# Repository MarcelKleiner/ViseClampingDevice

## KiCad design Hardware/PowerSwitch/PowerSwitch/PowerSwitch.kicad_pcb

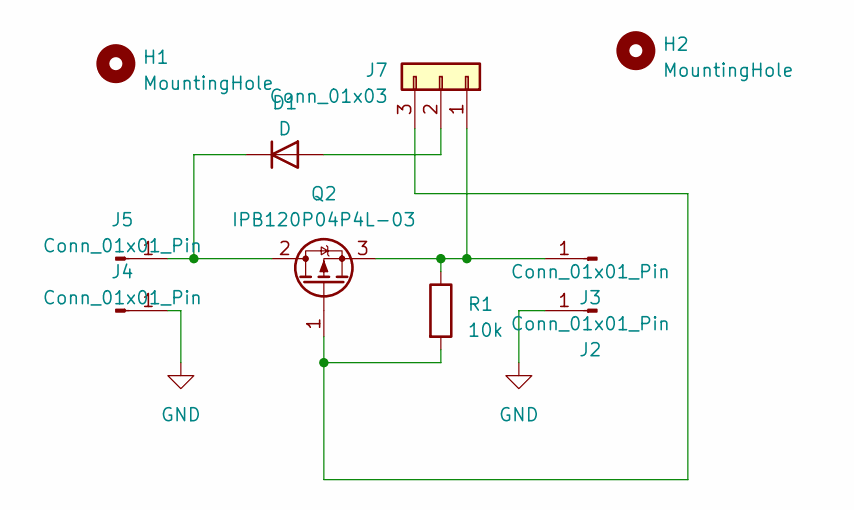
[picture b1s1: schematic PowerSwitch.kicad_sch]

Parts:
D1: D; D_1206_3216Metric
H1, H2: MountingHole; MountingHole_3.2mm_M3
J2, J3, J4, J5: Conn_01x01_Pin; MountingHole_3.2mm_M3_Pad_Via
J7: Conn_01x03; TerminalBlock_Phoenix_MPT-0,5-3-2.54_1x03_P2.54mm_Horizontal
Q2: IPB120P04P4L-03; TO-220-3_Vertical
R1: 10k; R_1206_3216Metric

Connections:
GND: J2.1, J4.1
unnamed: D1.2 (A), J7.2
unnamed: D1.1 (K), J5.1, Q2.2 (D)
unnamed: J3.1, J7.1, Q2.3 (S), R1.1
unnamed: J7.3, Q2.1 (G), R1.2

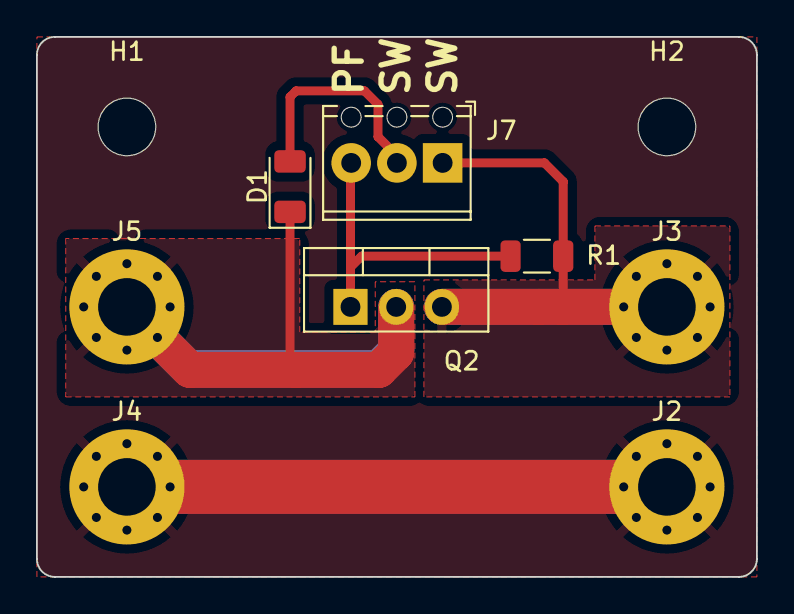
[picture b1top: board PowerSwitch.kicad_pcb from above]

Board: 2 copper layers, 40.0 x 30.0 mm, 10 parts (0 on the bottom side), 5 nets.

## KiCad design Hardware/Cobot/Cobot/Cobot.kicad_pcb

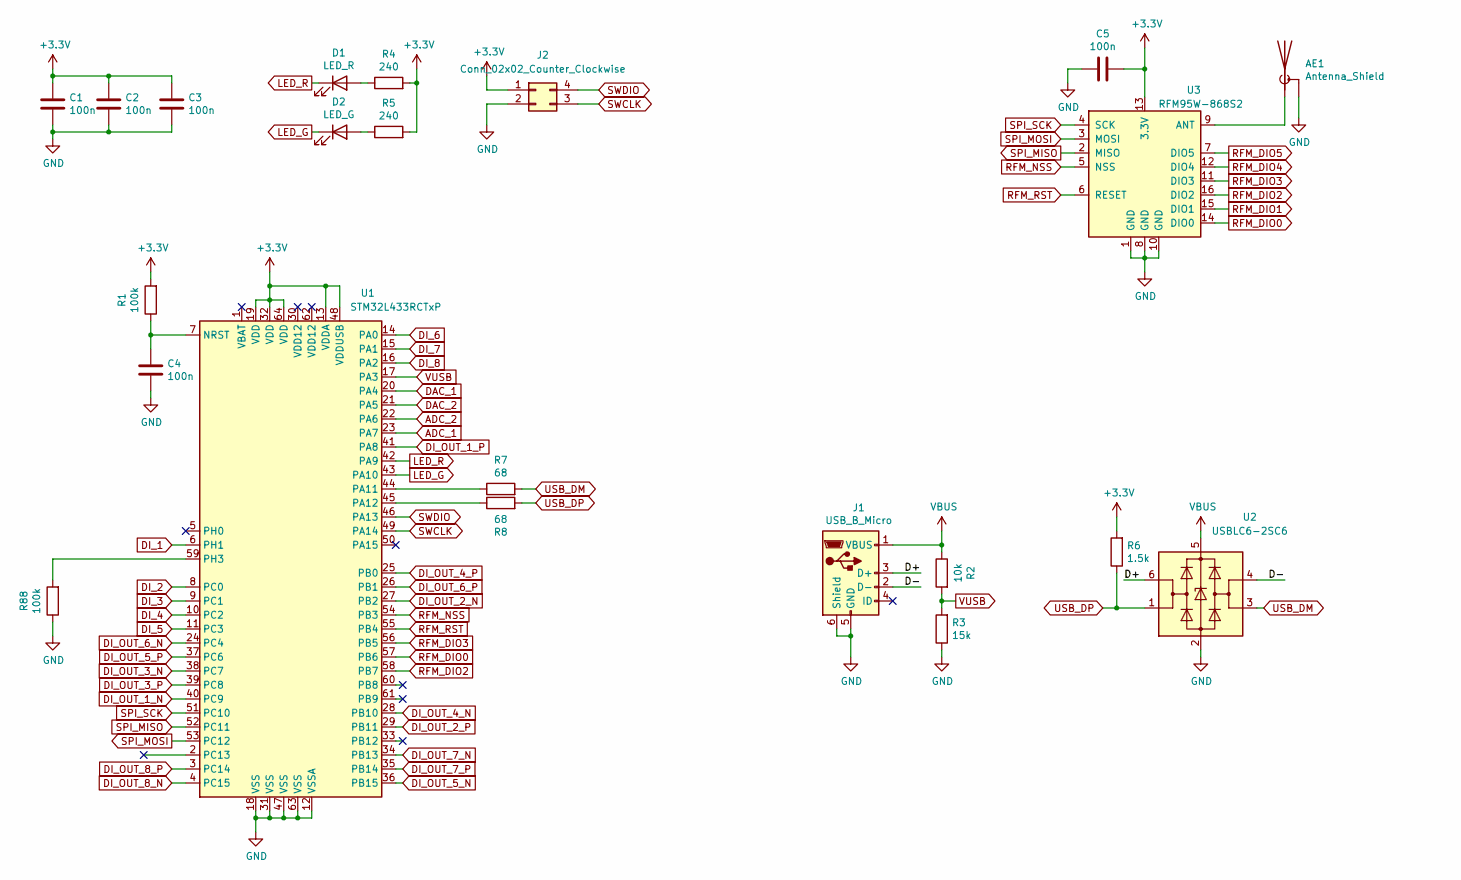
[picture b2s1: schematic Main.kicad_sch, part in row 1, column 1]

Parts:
AE1: Antenna_Shield; U.FL_Hirose_U.FL-R-SMT-1_Vertical; Mouser Nr. 712-CONUFL001-SMD-T
C1, C2, C3, C4, C5: 100n; C_0603_1608Metric; Mouser Nr. 187-CL10B104KB8NNWC
D1: LED_R; LED_0603_1608Metric; Mouser Nr. 696-SMLLXFP0603SICTR
D2: LED_G; LED_0603_1608Metric; Mouser Nr. 696-SMLLXFP0603SUGCT
J1: USB_B_Micro; USB_Micro-B_Wuerth_614105150721_Vertical; Mouser Nr. 710-614105150721
J2: Conn_02x02_Counter_Clockwise; PinHeader_2x02_P2.54mm_Vertical
R1, R88: 100k; R_0603_1608Metric; Mouser Nr. 71-CRCW0603100KFKEAC
R2: 10k; R_0603_1608Metric; Mouser Nr. 603-RT0603FRE0710KL
R3: 15k; R_0603_1608Metric; Mouser Nr. 667-ERJ-3EKF1502V
R4, R5: 240; R_0603_1608Metric; Mouser Nr. 603-RC0603FR-13240RL
R6: 1.5k; R_0603_1608Metric; Mouser Nr. 603-RT0603FRE101K5L
R7, R8: 68; R_0603_1608Metric; Mouser Nr. 603-RC0603JR-0768RL
U1: STM32L433RCTxP; LQFP-64_10x10mm_P0.5mm; Mouser Nr. 511-STM32L433RCT6P
U2: USBLC6-2SC6; SOT-23-6; Mouser Nr. 511-USBLC6-2SC6
U3: RFM95W-868S2; HOPERF_RFM9XW_SMD; Mouser Nr. 223-RFM95W-868S2

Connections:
+3.3V: C1.1, C2.1, C3.1, C5.2, J2.1, R1.2, R4.2, R5.2, R6.2, U1.13 (VDDA), U1.19 (VDD), U1.32 (VDD), U1.48 (VDDUSB), U1.64 (VDD), U3.13 (3.3V); also elsewhere on the board
/Main/D+: J1.3 (D+), U2.6 (I/O1)
/Main/D-: J1.2 (D-), U2.4 (I/O2)
ADC_1: U1.23 (PA7); also elsewhere on the board
ADC_2: U1.22 (PA6); also elsewhere on the board
DAC_1: U1.20 (PA4); also elsewhere on the board
DAC_2: U1.21 (PA5); also elsewhere on the board
DI_1: U1.6 (PH1); also elsewhere on the board
DI_2: U1.8 (PC0); also elsewhere on the board
DI_3: U1.9 (PC1); also elsewhere on the board
DI_4: U1.10 (PC2); also elsewhere on the board
DI_5: U1.11 (PC3); also elsewhere on the board
DI_6: U1.14 (PA0); also elsewhere on the board
DI_7: U1.15 (PA1); also elsewhere on the board
DI_8: U1.16 (PA2); also elsewhere on the board
DI_OUT_1_N: U1.40 (PC9); also elsewhere on the board
DI_OUT_1_P: U1.41 (PA8); also elsewhere on the board
DI_OUT_2_N: U1.27 (PB2); also elsewhere on the board
DI_OUT_2_P: U1.29 (PB11); also elsewhere on the board
DI_OUT_3_N: U1.38 (PC7); also elsewhere on the board
DI_OUT_3_P: U1.39 (PC8); also elsewhere on the board
DI_OUT_4_N: U1.28 (PB10); also elsewhere on the board
DI_OUT_4_P: U1.25 (PB0); also elsewhere on the board
DI_OUT_5_N: U1.36 (PB15); also elsewhere on the board
DI_OUT_5_P: U1.37 (PC6); also elsewhere on the board
DI_OUT_6_N: U1.24 (PC4); also elsewhere on the board
DI_OUT_6_P: U1.26 (PB1); also elsewhere on the board
DI_OUT_7_N: U1.34 (PB13); also elsewhere on the board
DI_OUT_7_P: U1.35 (PB14); also elsewhere on the board
DI_OUT_8_N: U1.4 (PC15); also elsewhere on the board
DI_OUT_8_P: U1.3 (PC14); also elsewhere on the board
LED_G: D2.1 (K), U1.43 (PA10)
LED_R: D1.1 (K), U1.42 (PA9)
unnamed: AE1.1 (A), U3.9 (ANT)
unnamed: D1.2 (A), R4.1
unnamed: D2.2 (A), R5.1
unnamed: C4.1, R1.1, U1.7 (NRST)
unnamed: R7.1, U1.44 (PA11)
unnamed: R8.1, U1.45 (PA12)
unnamed: R88.2, U1.59 (PH3)
RFM_DIO0: U1.57 (PB6), U3.14 (DIO0)
RFM_DIO1: U3.15 (DIO1)
RFM_DIO2: U1.58 (PB7), U3.16 (DIO2)
RFM_DIO3: U1.56 (PB5), U3.11 (DIO3)
RFM_DIO4: U3.12 (DIO4)
RFM_DIO5: U3.7 (DIO5)
RFM_NSS: U1.54 (PB3), U3.5 (NSS)
RFM_RST: U1.55 (PB4), U3.6 (RESET)
SPI_MISO: U1.52 (PC11), U3.2 (MISO)
SPI_MOSI: U1.53 (PC12), U3.3 (MOSI)
SPI_SCK: U1.51 (PC10), U3.4 (SCK)
SWCLK: J2.3, U1.49 (PA14)
SWDIO: J2.4, U1.46 (PA13)
USB_DM: R7.2, U2.3 (I/O2)
USB_DP: R6.1, R8.2, U2.1 (I/O1)
VBUS: J1.1 (VBUS), R2.1, U2.5 (VBUS); also elsewhere on the board
VUSB: R2.2, R3.2, U1.17 (PA3)

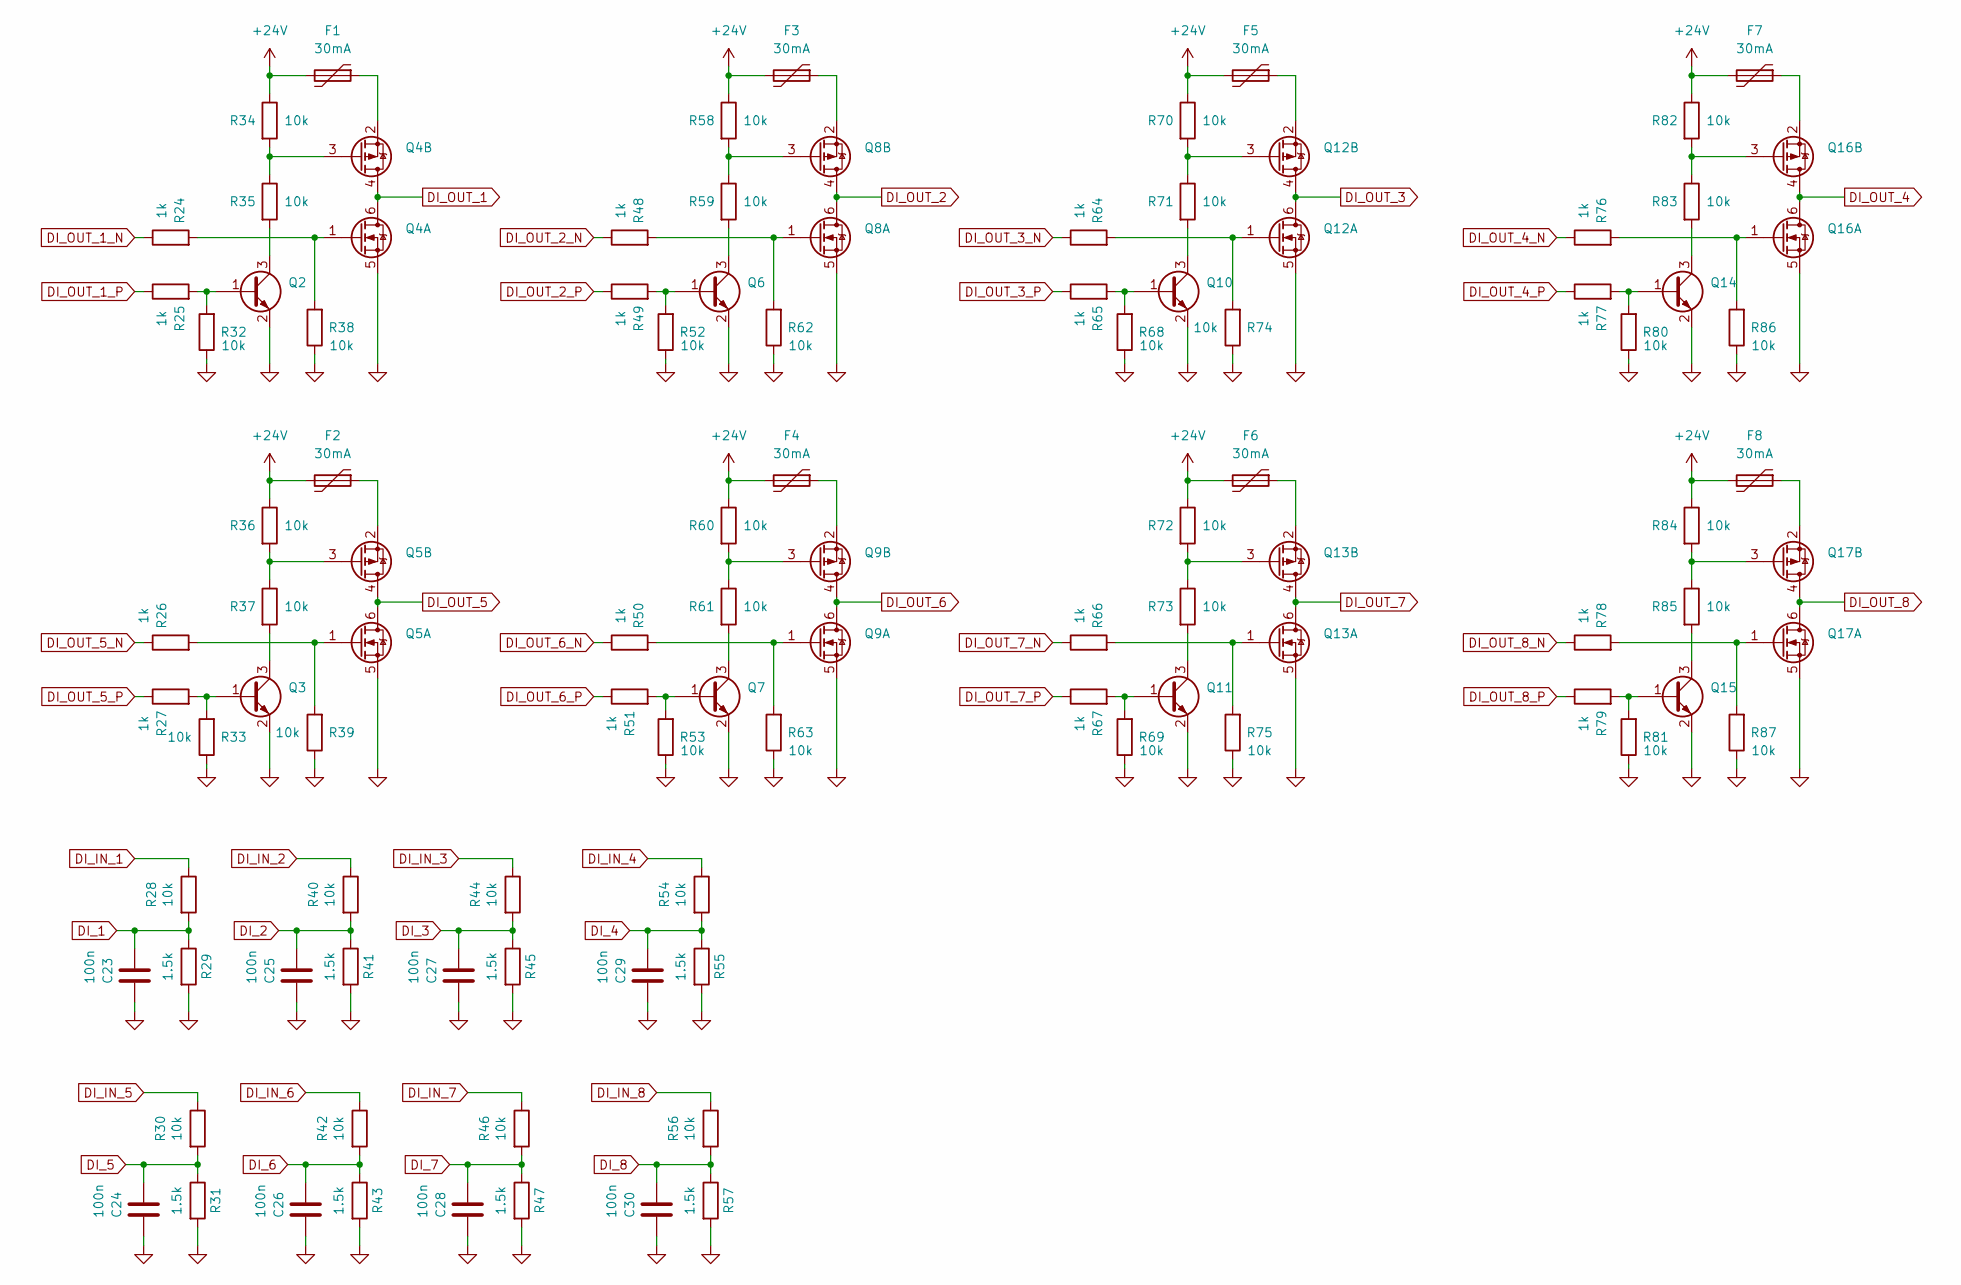
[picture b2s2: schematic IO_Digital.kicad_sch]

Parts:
C23, C24, C25, C26, C27, C28, C29, C30: 100n; C_0603_1608Metric; Mouser Nr. 187-CL10B104KB8NNWC
F1, F2, F3, F4, F5, F6, F7, F8: 30mA; Fuse_0603_1608Metric; Mouser Nr. 530-0ZCM0003FF2G
Q2, Q3, Q6, Q7, Q10, Q11, Q14, Q15: SOT-23; Mouser Nr. 771-BC846A235
Q4, Q5, Q8, Q9, Q12, Q13, Q16, Q17: SOT-23-6; Mouser Nr. 621-DMC2700UDM-7
R24, R25, R26, R27, R48, R49, R50, R51, R64, R65, R66, R67, R76, R77, R78, R79: 1k; R_0603_1608Metric; Mouser Nr. 603-RT0603FRE071KL
R28, R30, R32, R33, R34, R35, R36, R37, R38, R39, R40, R42, R44, R46, R52, R53, R54, R56, R58, R59, R60, R61, R62, R63, R68, R69, R70, R71, R72, R73, R74, R75, R80, R81, R82, R83, R84, R85, R86, R87: 10k; R_0603_1608Metric; Mouser Nr. 603-RT0603FRE0710KL
R29, R31, R41, R43, R45, R47, R55, R57: 1.5k; R_0603_1608Metric; Mouser Nr. 603-RT0603FRE101K5L

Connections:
+24V: F1.2, F2.2, F3.2, F4.2, F5.2, F6.2, F7.2, F8.2, R34.1, R36.1, R58.1, R60.1, R70.1, R72.1, R82.1, R84.1; also elsewhere on the board
DI_1: C23.1, R28.2, R29.1; also elsewhere on the board
DI_2: C25.1, R40.2, R41.1; also elsewhere on the board
DI_3: C27.1, R44.2, R45.1; also elsewhere on the board
DI_4: C29.1, R54.2, R55.1; also elsewhere on the board
DI_5: C24.1, R30.2, R31.1; also elsewhere on the board
DI_6: C26.1, R42.2, R43.1; also elsewhere on the board
DI_7: C28.1, R46.2, R47.1; also elsewhere on the board
DI_8: C30.1, R56.2, R57.1; also elsewhere on the board
DI_IN_1: R28.1; also elsewhere on the board
DI_IN_2: R40.1; also elsewhere on the board
DI_IN_3: R44.1; also elsewhere on the board
DI_IN_4: R54.1; also elsewhere on the board
DI_IN_5: R30.1; also elsewhere on the board
DI_IN_6: R42.1; also elsewhere on the board
DI_IN_7: R46.1; also elsewhere on the board
DI_IN_8: R56.1; also elsewhere on the board
DI_OUT_1: Q4.4 (D), Q4.6 (D); also elsewhere on the board
DI_OUT_1_N: R24.1; also elsewhere on the board
DI_OUT_1_P: R25.1; also elsewhere on the board
DI_OUT_2: Q8.4 (D), Q8.6 (D); also elsewhere on the board
DI_OUT_2_N: R48.1; also elsewhere on the board
DI_OUT_2_P: R49.1; also elsewhere on the board
DI_OUT_3: Q12.4 (D), Q12.6 (D); also elsewhere on the board
DI_OUT_3_N: R64.1; also elsewhere on the board
DI_OUT_3_P: R65.1; also elsewhere on the board
DI_OUT_4: Q16.4 (D), Q16.6 (D); also elsewhere on the board
DI_OUT_4_N: R76.1; also elsewhere on the board
DI_OUT_4_P: R77.1; also elsewhere on the board
DI_OUT_5: Q5.4 (D), Q5.6 (D); also elsewhere on the board
DI_OUT_5_N: R26.1; also elsewhere on the board
DI_OUT_5_P: R27.1; also elsewhere on the board
DI_OUT_6: Q9.4 (D), Q9.6 (D); also elsewhere on the board
DI_OUT_6_N: R50.1; also elsewhere on the board
DI_OUT_6_P: R51.1; also elsewhere on the board
DI_OUT_7: Q13.4 (D), Q13.6 (D); also elsewhere on the board
DI_OUT_7_N: R66.1; also elsewhere on the board
DI_OUT_7_P: R67.1; also elsewhere on the board
DI_OUT_8: Q17.4 (D), Q17.6 (D); also elsewhere on the board
DI_OUT_8_N: R78.1; also elsewhere on the board
DI_OUT_8_P: R79.1; also elsewhere on the board
unnamed: Q2.1 (B), R25.2, R32.2
unnamed: Q2.3 (C), R35.2
unnamed: Q3.1 (B), R27.2, R33.2
unnamed: Q3.3 (C), R37.2
unnamed: Q4.1 (G), R24.2, R38.2
unnamed: Q4.3 (G), R34.2, R35.1
unnamed: F1.1, Q4.2 (S)
unnamed: Q5.1 (G), R26.2, R39.2
unnamed: Q5.3 (G), R36.2, R37.1
unnamed: F2.1, Q5.2 (S)
unnamed: Q6.1 (B), R49.2, R52.2
unnamed: Q6.3 (C), R59.2
unnamed: Q7.1 (B), R51.2, R53.2
unnamed: Q7.3 (C), R61.2
unnamed: Q8.1 (G), R48.2, R62.2
unnamed: Q8.3 (G), R58.2, R59.1
unnamed: F3.1, Q8.2 (S)
unnamed: Q9.1 (G), R50.2, R63.2
unnamed: Q9.3 (G), R60.2, R61.1
unnamed: F4.1, Q9.2 (S)
unnamed: Q10.1 (B), R65.2, R68.2
unnamed: Q10.3 (C), R71.2
unnamed: Q11.1 (B), R67.2, R69.2
unnamed: Q11.3 (C), R73.2
unnamed: Q12.1 (G), R64.2, R74.2
unnamed: Q12.3 (G), R70.2, R71.1
unnamed: F5.1, Q12.2 (S)
unnamed: Q13.1 (G), R66.2, R75.2
unnamed: Q13.3 (G), R72.2, R73.1
unnamed: F6.1, Q13.2 (S)
unnamed: Q14.1 (B), R77.2, R80.2
unnamed: Q14.3 (C), R83.2
unnamed: Q15.1 (B), R79.2, R81.2
unnamed: Q15.3 (C), R85.2
unnamed: Q16.1 (G), R76.2, R86.2
unnamed: Q16.3 (G), R82.2, R83.1
unnamed: F7.1, Q16.2 (S)
unnamed: Q17.1 (G), R78.2, R87.2
unnamed: Q17.3 (G), R84.2, R85.1
unnamed: F8.1, Q17.2 (S)

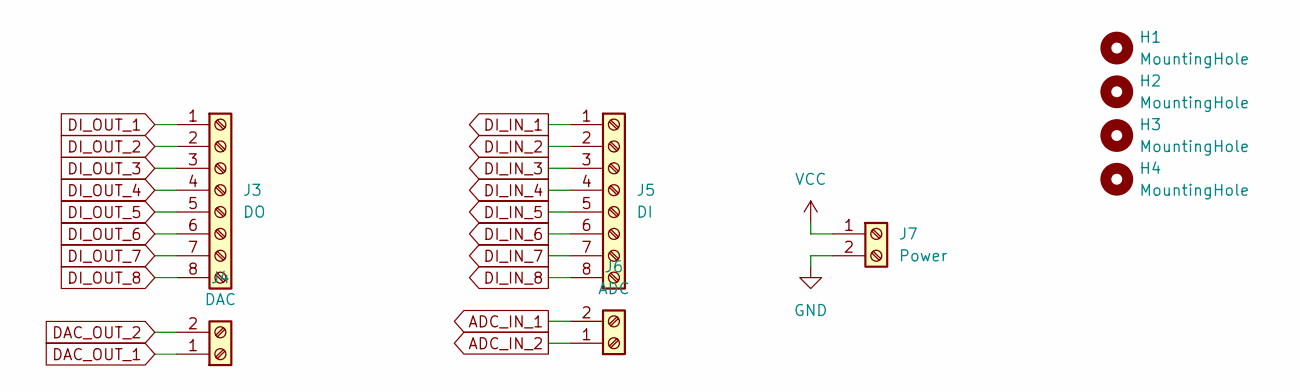
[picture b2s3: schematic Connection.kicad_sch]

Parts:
H1, H2, H3, H4: MountingHole; MountingHole_3.2mm_M3
J3: DO; TerminalBlock_Phoenix_MPT-0,5-8-2.54_1x08_P2.54mm_Horizontal
J4: DAC; TerminalBlock_Phoenix_MPT-0,5-2-2.54_1x02_P2.54mm_Horizontal
J5: DI; TerminalBlock_Phoenix_MPT-0,5-8-2.54_1x08_P2.54mm_Horizontal
J6: ADC; TerminalBlock_Phoenix_MPT-0,5-2-2.54_1x02_P2.54mm_Horizontal
J7: Power; TerminalBlock_Phoenix_MPT-0,5-2-2.54_1x02_P2.54mm_Horizontal

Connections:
ADC_IN_1: J6.2; also elsewhere on the board
ADC_IN_2: J6.1; also elsewhere on the board
DAC_OUT_1: J4.1; also elsewhere on the board
DAC_OUT_2: J4.2; also elsewhere on the board
DI_IN_1: J5.1; also elsewhere on the board
DI_IN_2: J5.2; also elsewhere on the board
DI_IN_3: J5.3; also elsewhere on the board
DI_IN_4: J5.4; also elsewhere on the board
DI_IN_5: J5.5; also elsewhere on the board
DI_IN_6: J5.6; also elsewhere on the board
DI_IN_7: J5.7; also elsewhere on the board
DI_IN_8: J5.8; also elsewhere on the board
DI_OUT_1: J3.1; also elsewhere on the board
DI_OUT_2: J3.2; also elsewhere on the board
DI_OUT_3: J3.3; also elsewhere on the board
DI_OUT_4: J3.4; also elsewhere on the board
DI_OUT_5: J3.5; also elsewhere on the board
DI_OUT_6: J3.6; also elsewhere on the board
DI_OUT_7: J3.7; also elsewhere on the board
DI_OUT_8: J3.8; also elsewhere on the board
VCC: J7.1; also elsewhere on the board

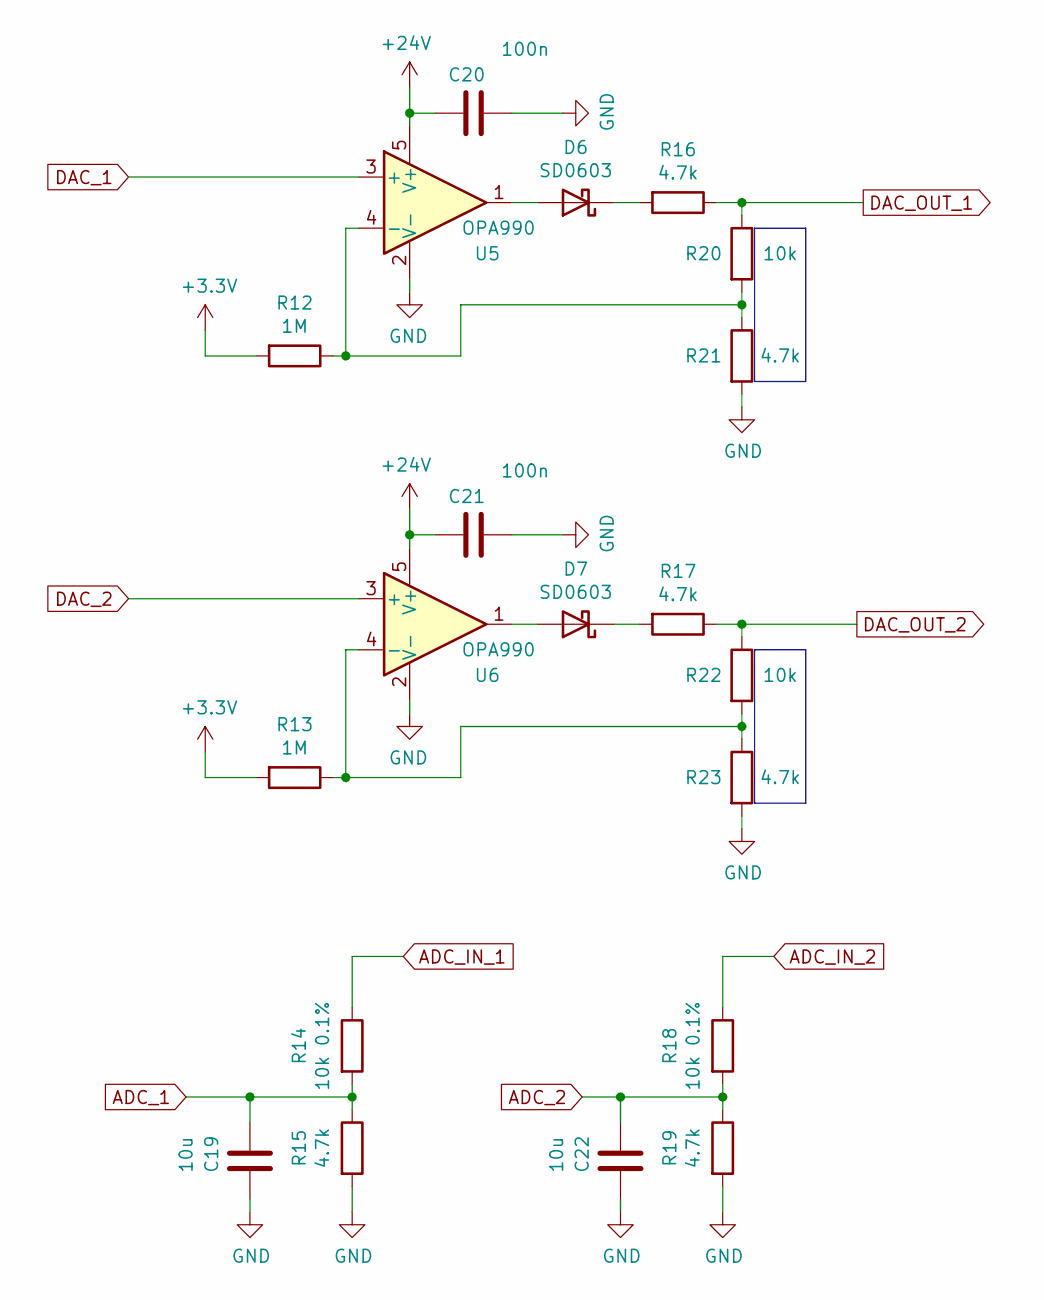
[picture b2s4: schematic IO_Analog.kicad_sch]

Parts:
C19, C22: 10u; C_0603_1608Metric; Mouser Nr. 187-CL10A106MA8NRNC
C20, C21: 100n; C_0603_1608Metric; Mouser Nr. 187-CL10B104KB8NNWC
D6, D7: SD0603; D_0603_1608Metric; Mouser Nr. 581-SD0603S040S0R2
R12, R13: 1M; R_0603_1608Metric; Mouser Nr. 667-ERJ-3GEYJ105V
R14, R18: 10k 0.1%; R_0603_1608Metric; Mouser Nr. 284-APC0603B10K0N
R15, R16, R17, R19, R21, R23: 4.7k; R_0603_1608Metric; Mouser Nr. 603-RT0603FRE074K7L
R20, R22: 10k; R_0603_1608Metric; Mouser Nr. 603-RT0603FRE0710KL
U5, U6: OPA990; SOT-23-5; Mouser Nr. 595-OPA990IDBVR

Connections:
+3.3V: R12.2, R13.2; also elsewhere on the board
+24V: C20.1, C21.1, U5.5 (V+), U6.5 (V+); also elsewhere on the board
ADC_1: C19.1, R14.2, R15.1; also elsewhere on the board
ADC_2: C22.1, R18.2, R19.1; also elsewhere on the board
ADC_IN_1: R14.1; also elsewhere on the board
ADC_IN_2: R18.1; also elsewhere on the board
DAC_1: U5.3 (+); also elsewhere on the board
DAC_2: U6.3 (+); also elsewhere on the board
DAC_OUT_1: R16.1, R20.1; also elsewhere on the board
DAC_OUT_2: R17.1, R22.1; also elsewhere on the board
unnamed: D6.2 (A), U5.1
unnamed: D6.1 (K), R16.2
unnamed: D7.2 (A), U6.1
unnamed: D7.1 (K), R17.2
unnamed: R12.1, R20.2, R21.1, U5.4 (-)
unnamed: R13.1, R22.2, R23.1, U6.4 (-)

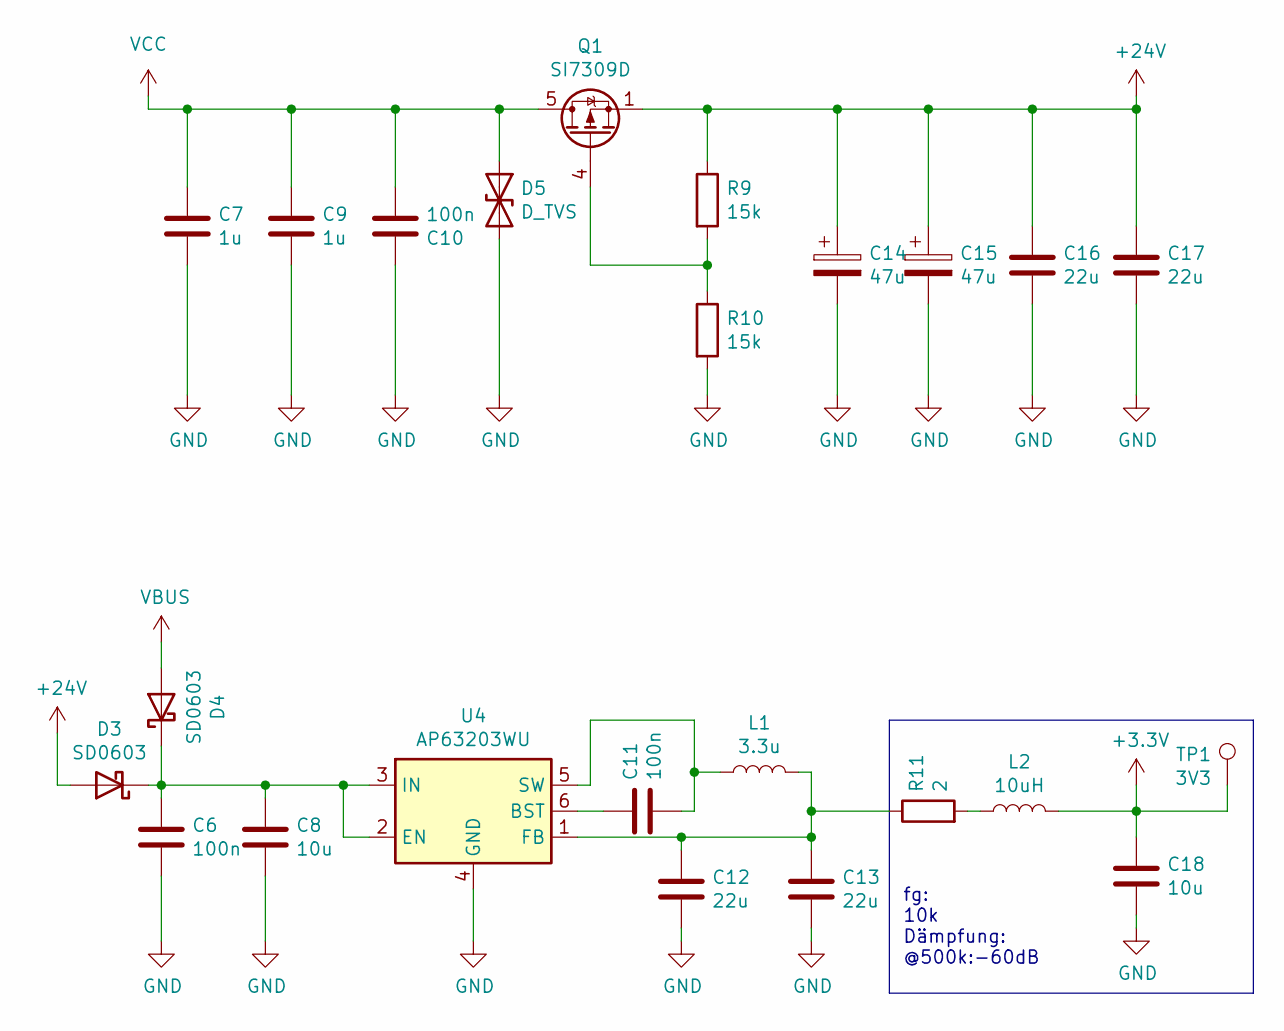
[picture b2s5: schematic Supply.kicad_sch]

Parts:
C6, C10, C11: 100n; C_0603_1608Metric; Mouser Nr. 187-CL10B104KB8NNWC
C7, C9: 1u; C_0603_1608Metric; Mouser Nr. 187-CL10A105KA8NFNC
C8, C18: 10u; C_0603_1608Metric; Mouser Nr. 187-CL10A106MA8NRNC
C12, C13, C16, C17: 22u; C_0805_2012Metric; Mouser Nr. 187-CL21A226MAYNNNE
C14, C15: 47u; CP_Elec_5x5.8; Mouser Nr. 667-EEE-FT1V470AR
D3, D4: SD0603; D_0603_1608Metric; Mouser Nr. 581-SD0603S040S0R2
D5: D_TVS; D_0603_1608Metric
L1: 3.3u; L_0805_2012Metric; Mouser Nr. 70-IMC0805ER3R3J01
L2: 10uH; L_0603_1608Metric; Mouser Nr. 81-LQM18DH100M70L
Q1: SI7309D; Vishay_PowerPAK_1212-8_Single; Mouser Nr. 781-SI7309DN-T1-E3
R9, R10: 15k; R_0603_1608Metric; Mouser Nr. 667-ERJ-3EKF1502V
R11: 2; R_0603_1608Metric; Mouser Nr. 652-CR0603-J/-2R0ELF
TP1: 3V3; TestPoint_Pad_D1.0mm
U4: AP63203WU; SOT-23-6; Mouser Nr. 621-AP63203WU-7

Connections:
+3.3V: C18.2, L2.2, TP1.1; also elsewhere on the board
+24V: C14.1, C15.1, C16.2, C17.2, D3.2 (A), Q1.1 (S), Q1.2 (S), Q1.3 (S), R9.1; also elsewhere on the board
unnamed: C6.1, C8.1, D3.1 (K), D4.1 (K), U4.2 (EN), U4.3 (IN)
unnamed: L2.1, R11.2
unnamed: Q1.4 (G), R9.2, R10.1
unnamed: C11.2, U4.6 (BST)
unnamed: C12.2, C13.2, L1.2, R11.1, U4.1 (FB)
unnamed: C11.1, L1.1, U4.5 (SW)
VBUS: D4.2 (A); also elsewhere on the board
VCC: C7.2, C9.2, C10.1, D5.1 (A1), Q1.5 (D); also elsewhere on the board

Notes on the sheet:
fg: 10k Dämpfung: @500k:-60dB

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
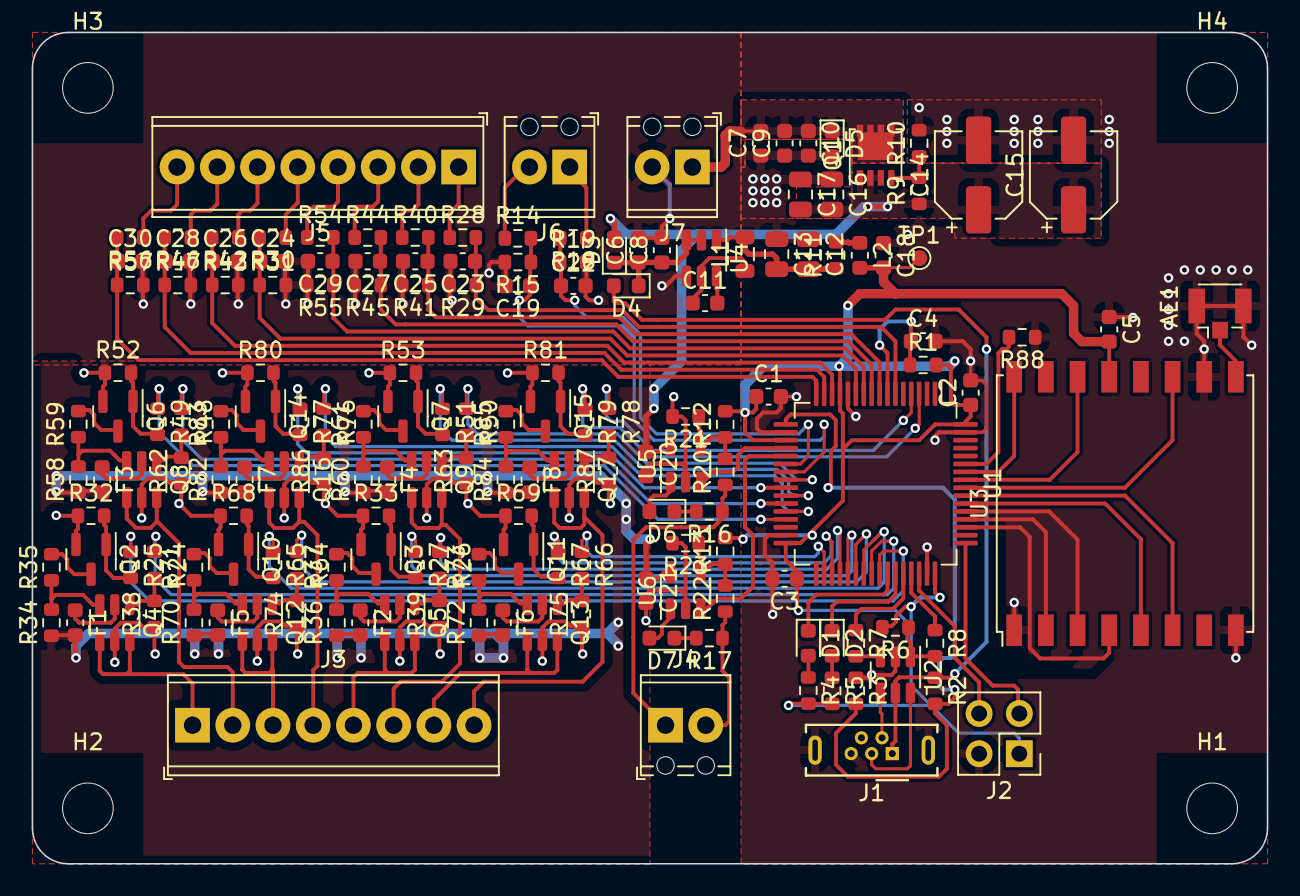
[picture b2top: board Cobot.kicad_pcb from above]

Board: 2 copper layers, 78.0 x 52.5 mm, 171 parts (0 on the bottom side), 129 nets.

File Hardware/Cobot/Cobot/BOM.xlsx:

Spalte1 | Spalte2 | Spalte3 | Spalte4 | Spalte5 | Spalte6 | Spalte7 | Spalte8 | Spalte9
Item | Qty | Reference(s) | Value | LibPart | Footprint | Datasheet | Hersteller Nr. | Mouser Nr.
1 | 1 | AE1 | Antenna_Shield | Device:Antenna_Shield | Connector_Coaxial:U.FL_Hirose_U.FL-R-SMT-1_Vertical | https://www.mouser.ch/datasheet/2/238/LNNC_S_A0004847293_1-2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 | CONUFL001-SMD-T | 712-CONUFL001-SMD-T
2 | 18 | C1, C2, C3, C4, C5, C6, C10, C11, C20, C21, C23, C24, C25, C26, C27, C28, C29, 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 | 100n | Device:C | Capacitor_SMD:C_0603_1608Metric | https://www.mouser.ch/datasheet/2/585/MLCC-1837944.pdf | CL10B104KB8NNWC | 187-CL10B104KB8NNWC
3 | 2 | C7, C9 | 1u | Device:C | Capacitor_SMD:C_0603_1608Metric | https://www.mouser.ch/ProductDetail/Samsung-Electro-Mechanic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 | CL10A105KA8NFNC | 187-CL10A105KA8NFNC
4 | 4 | C8, C18, C19, C22 | 10u | Device:C | Capacitor_SMD:C_0603_1608Metric | https://www.mouser.ch/datasheet/2/585/MLCC-1837944.pdf | CL10A106MA8NRNC | 187-CL10A106MA8NRNC
5 | 4 | C12, C13, C16, C17 | 22u | Device:C | Capacitor_SMD:C_0805_2012Metric | https://www.mouser.ch/datasheet/2/585/MLCC-1837944.pdf | CL21A226MAYNNNE | 187-CL21A226MAYNNNE
6 | 2 | C14, C15 | 47u | Device:C_Polarized | Capacitor_SMD:CP_Elec_5x5.8 | https://www.mouser.ch/datasheet/2/315/ABA0000C1240-1130326.pdf | EEE-FT1V470AR | 667-EEE-FT1V470AR
7 | 1 | D1 | LED_R | Device:LED | LED_SMD:LED_0603_1608Metric | https://www.lumex.com/datasheet/SML-LXFP0603SICATR | SML-LXFP0603SIC-TR | 696-SMLLXFP0603SICTR
8 | 1 | D2 | LED_G | Device:LED | LED_SMD:LED_0603_1608Metric | https://www.mouser.ch/datasheet/2/244/SML-LXFP0603SUGCTR-113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 | SML-LXFP0603SUGCTR | 696-SMLLXFP0603SUGCT
9 | 4 | D3, D4, D6, D7 | SD0603 | Device:D_Schottky | Diode_SMD:D_0603_1608Metric | https://www.mouser.ch/datasheet/2/40/schottky-776407.pdf | SD0603S040S0R2 | 581-SD0603S040S0R2
10 | 1 | D5 | D_TVS | Device:D_TVS | Diode_SMD:D_0603_1608Metric | ~
11 | 8 | F1, F2, F3, F4, F5, F6, F7, F8 | 30mA | Device:Polyfuse | Fuse:Fuse_0603_1608Metric | https://www.mouser.ch/datasheet/2/643/ds-CP-0zcm-series-1313124.pdf | 0ZCM0003FF2G | 530-0ZCM0003FF2G
12 | 4 | H1, H2, H3, H4 | MountingHole | Mechanical:MountingHole | MountingHole:MountingHole_3.2mm_M3 | ~
13 | 1 | J1 | USB_B_Micro | Connector:USB_B_Micro | Connector_USB:USB_Micro-B_Wuerth_614105150721_Vertical | https://www.mouser.ch/datasheet/2/445/614105150721-1717916.pdf | 614105150721 | 710-614105150721
14 | 1 | J2 | Conn_02x02_Counter_Clockwise | Connector_Generic:Conn_02x02_Counter_Clockwise | Connector_PinHeader_2.54mm:PinHeader_2x02_P2.54mm_Vertical | ~
15 | 1 | J3 | DO | Connector:Screw_Terminal_01x08 | MK_Footprints:TerminalBlock_Phoenix_MPT-0,5-8-2.54_1x08_P2.54mm_Horizontal | ~
16 | 1 | J4 | DAC | Connector:Screw_Terminal_01x02 | MK_Footprints:TerminalBlock_Phoenix_MPT-0,5-2-2.54_1x02_P2.54mm_Horizontal | ~
17 | 1 | J5 | DI | Connector:Screw_Terminal_01x08 | MK_Footprints:TerminalBlock_Phoenix_MPT-0,5-8-2.54_1x08_P2.54mm_Horizontal | ~
18 | 1 | J6 | ADC | Connector:Screw_Terminal_01x02 | MK_Footprints:TerminalBlock_Phoenix_MPT-0,5-2-2.54_1x02_P2.54mm_Horizontal | ~
19 | 1 | J7 | Power | Connector:Screw_Terminal_01x02 | MK_Footprints:TerminalBlock_Phoenix_MPT-0,5-2-2.54_1x02_P2.54mm_Horizontal | ~
20 | 1 | L1 | 3.3u | Device:L | Inductor_SMD:L_0805_2012Metric | https://www.mouser.ch/datasheet/2/427/imc08051-1763337.pdf | IMC0805ER3R3J01 | 70-IMC0805ER3R3J01
21 | 1 | L2 | 10uH | Device:L | Inductor_SMD:L_0603_1608Metric | https://www.mouser.ch/datasheet/2/281/LQM18DH100M70_23-1948371.pdf | LQM18DH100M70L | 81-LQM18DH100M70L
22 | 1 | Q1 | SI7309D | Transistor_FET:SiS415DNT | Package_SO:Vishay_PowerPAK_1212-8_Single | https://www.mouser.ch/datasheet/2/427/73434-1766021.pdf | SI7309DN-T1-E3 | 781-SI7309DN-T1-E3
23 | 8 | Q2, Q3, Q6, Q7, Q10, Q11, Q14, Q15 | ~ | Transistor_BJT:BC846 | Package_TO_SOT_SMD:SOT-23 | https://assets.nexperia.com/documents/data-sheet/BC846_SER.pdf | BC846A,235 | 771-BC846A235
24 | 8 | Q4, Q5, Q8, Q9, Q12, Q13, Q16, Q17 | ~ | Transistor_FET:DMC3071LVT | Package_TO_SOT_SMD:SOT-23-6 | https://www.diodes.com/assets/Datasheets/DMC3071LVT.pdf | DMC2700UDM-7 | 621-DMC2700UDM-7
25 | 1 | R1 | 100k | Device:R | Resistor_SMD:R_0603_1608Metric | https://www.mouser.ch/datasheet/2/427/crcwce3-1762584.pdf | CRCW0603100KFKEAC | 71-CRCW0603100KFKEAC
26 | 43 | R2, R20, R22, R28, R30, R32, R33, R34, R35, R36, R37, R38, R39, R40, R42, R44, 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 | 10k | Device:R | Resistor_SMD:R_0603_1608Metric | https://www.mouser.ch/datasheet/2/447/PYu_RT_1_to_0_01_RoHS_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 | RT0603FRE0710KL | 603-RT0603FRE0710KL
27 | 3 | R3, R9, R10 | 15k | Device:R | Resistor_SMD:R_0603_1608Metric | https://www.mouser.ch/datasheet/2/315/AOA0000C304-1149620.pdf | ERJ-3EKF1502V | 667-ERJ-3EKF1502V
28 | 2 | R4, R5 | 240 | Device:R | Resistor_SMD:R_0603_1608Metric | https://www.mouser.ch/datasheet/2/447/PYu_RC_Group_51_RoHS_L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 | RC0603FR-13240RL | 603-RC0603FR-13240RL
29 | 9 | R6, R29, R31, R41, R43, R45, R47, R55, R57 | 1.5k | Device:R | Resistor_SMD:R_0603_1608Metric | https://www.mouser.ch/datasheet/2/447/PYu_RT_1_to_0_01_RoHS_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 | RT0603FRE101K5L | 603-RT0603FRE101K5L
30 | 2 | R7, R8 | 68 | Device:R | Resistor_SMD:R_0603_1608Metric | https://www.mouser.ch/datasheet/2/447/PYu_RC_Group_51_RoHS_L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 | CRCW060368R0FKEA | 603-RC0603JR-0768RL
31 | 1 | R11 | 2 | Device:R | Resistor_SMD:R_0603_1608Metric | https://www.mouser.ch/datasheet/2/54/cr-1858361.pdf | CR0603-J/-2R0ELF | 652-CR0603-J/-2R0ELF
32 | 2 | R12, R13 | 1M | Device:R | Resistor_SMD:R_0603_1608Metric | https://www.mouser.ch/datasheet/2/315/AOA0000C301-1488782.pdf | ERJ-3GEYJ105V | 667-ERJ-3GEYJ105V
33 | 2 | R14, R18 | 10k 0.1% | Device:R | Resistor_SMD:R_0603_1608Metric | https://www.mouser.ch/datasheet/2/303/APC-1-15.34-911303.pdf | APC0603B10K0N | 284-APC0603B10K0N
34 | 6 | R15, R16, R17, R19, R21, R23 | 4.7k | Device:R | Resistor_SMD:R_0603_1608Metric | https://www.mouser.ch/datasheet/2/447/PYu_RT_1_to_0_01_RoHS_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 | RT0603FRE074K7 | 603-RT0603FRE074K7L
35 | 16 | R24, R25, R26, R27, R48, R49, R50, R51, R64, R65, R66, R67, R76, R77, R78, R79 | 1k | Device:R | Resistor_SMD:R_0603_1608Metric | https://www.mouser.ch/datasheet/2/447/PYu_RT_1_to_0_01_RoHS_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 | RT0603FRE071KL | 603-RT0603FRE071KL
36 | 1 | TP1 | 3V3 | Connector:TestPoint | TestPoint:TestPoint_Pad_D1.0mm | ~
37 | 1 | U1 | STM32L433RCTxP | MCU_ST_STM32L4:STM32L433RCTxP | Package_QFP:LQFP-64_10x10mm_P0.5mm | https://www.mouser.ch/datasheet/2/389/dm00257192-1798730.pdf | STM32L433RCT6P | 511-STM32L433RCT6P
38 | 1 | U2 | USBLC6-2SC6 | Power_Protection:USBLC6-2SC6 | Package_TO_SOT_SMD:SOT-23-6 | http://www2.st.com/resource/en/datasheet/CD00050750.pdf | USBLC6-2SC6 | 511-USBLC6-2SC6
39 | 1 | U3 | RFM95W-868S2 | Heissluftballon-rescue:RFM95W-868S2-RF_AM_FM | RF_Module:HOPERF_RFM9XW_SMD | https://www.mouser.ch/datasheet/2/975/1463993415RFM95_96_97_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 | RFM95W-868S2 | 223-RFM95W-868S2
40 | 1 | U4 | AP63203WU | Regulator_Switching:AP63203WU | Package_TO_SOT_SMD:SOT-23-6 | https://www.mouser.ch/ProductDetail/Diodes-Incorporated/AP63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 | AP63203WU-7 | 621-AP63203WU-7
41 | 2 | U5, U6 | OPA990 | Amplifier_Operational:OPA330xxDBV | Package_TO_SOT_SMD:SOT-23-5 | https://www.ti.com/lit/ds/symlink/opa990.pdf | OPA990IDBVR | 595-OPA990IDBVR

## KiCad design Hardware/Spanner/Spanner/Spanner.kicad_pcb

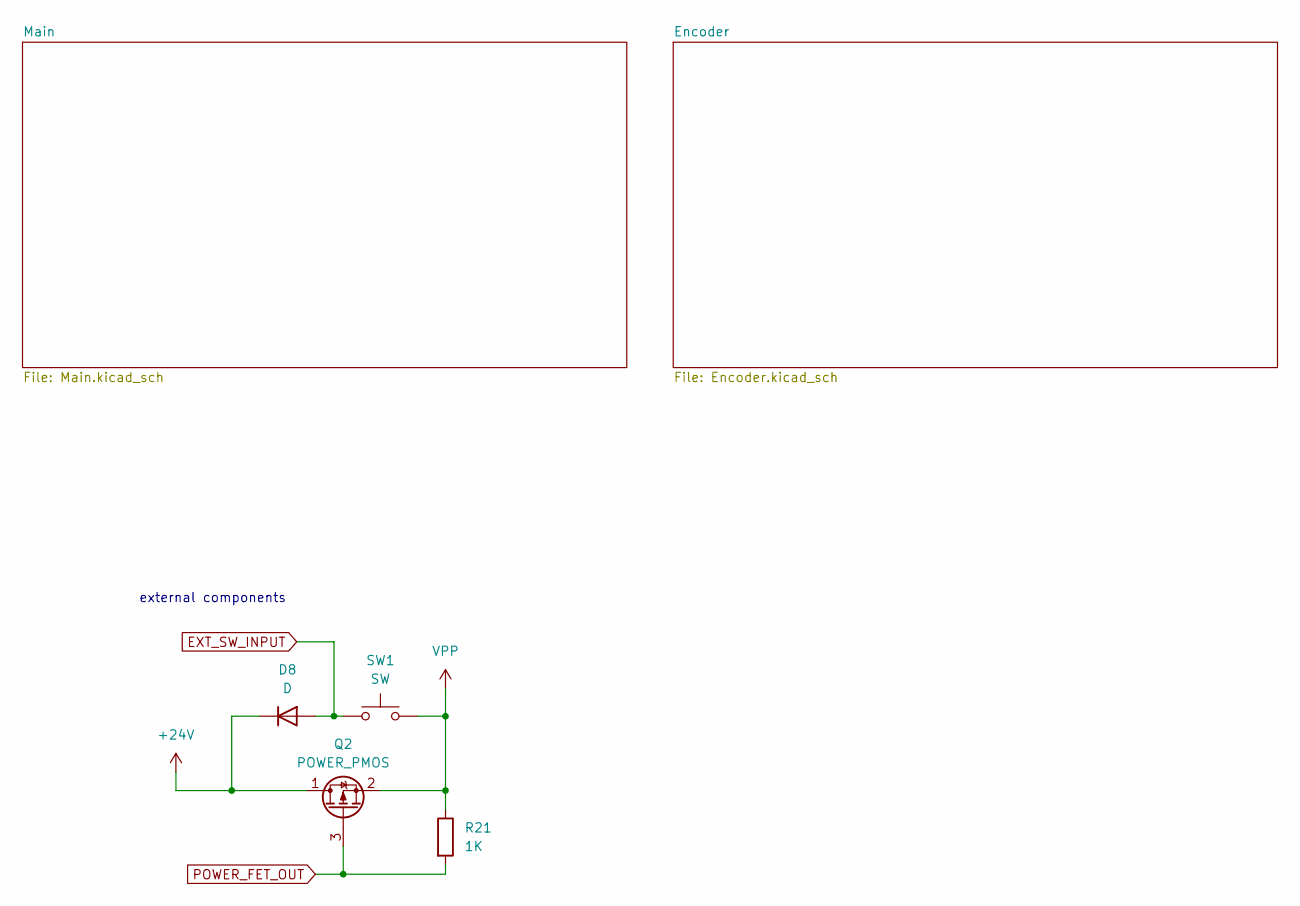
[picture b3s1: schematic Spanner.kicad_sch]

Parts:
D8: D
Q2: POWER_PMOS
R21: 1K
SW1: SW

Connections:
unnamed: D8.1 (K), Q2.1 (D)
unnamed: D8.2 (A), SW1.1 (A), SW1.2 (A)
unnamed: Q2.2 (S), R21.1, SW1.3 (B), SW1.4 (B)
unnamed: Q2.3 (G), R21.2

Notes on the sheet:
external components
